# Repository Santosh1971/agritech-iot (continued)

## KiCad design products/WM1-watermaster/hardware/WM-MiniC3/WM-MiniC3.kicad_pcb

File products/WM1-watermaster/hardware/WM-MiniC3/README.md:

# WM-Mini C3 rev A: pump, doser and 4-valve controller (2026-10-27)

A larger FG1. An ESP32-C3 Super Mini (plug-in, USB-C powered) drives six SRD relays through a ULN2003A:
- **K1 PUMP** and **K2 DOSER** switch 230 V.
- **K3–K6** switch 12/24 VAC valves, with one common.

It also has a Hall flow input, a DS1307 RTC with a CR2032, and seven LEDs. The plan and the decisions behind it are in [SPEC.md](SPEC.md) (draft 0.3) and on the "WM-Mini C3 Plan" page.

## Status

| Item | State |
|---|---|
| Schematic | Generated from `tools/design.py`, with wires inside each block and labels only between blocks. **ERC: 0 errors, 0 warnings.** |
| PCB | 99 × 48 mm, 2 layers. Routed with Freerouting, zones filled. **DRC at every severity: 0 violations, 0 unconnected, schematic parity clean** (kicad-cli 9.0.7). |
| 230 V | 5 mm from the pump/doser copper (including their NC pins, which are live while off) to all other copper, enforced by `WM-MiniC3.kicad_dru`. The exceptions are inside K1/K2: 3.5 mm to their own coil pins (the SRD's pinout gives 3.6 mm), and 2.4 mm between pump and doser (the 5.08 mm header has 2.48 mm between its own pads). |
| Panel | `panel/WM-MiniC3-panel.kicad_pcb`, 99 × 98 mm: 2 boards and a 2 mm routed slot with 3 plain tabs (no V-cut, no mouse bites). Board 1 is turned 180°, so both connector edges face outwards. |
| Fab | `fab/`: panel and board Gerbers, schematic PDF, 1:1 prints (top and bottom), BOM, STEP and renders. **Order `WM-MiniC3-panel-gerbers.zip`.** |

## Layout

The board is the draft 0.3 plan **mirrored left to right**. On an upright SRD the NO pin comes out on the left. With the 230 V corner on the left, the pump and doser NO and COM run straight down into their headers without crossing, and still keep 5 mm from the valve header.

- **Bottom left:** K1 PUMP and K2 DOSER, upright, directly above J2 and J3.
- **Top left, above the relays they drive (all > 5 mm from 230 V):**
  - the ULN2003;
  - the six relay LEDs (P D V1 V2 V3 V4) and their resistors;
  - C1, 1000 µF / 16 V (10 mm, 5 mm pitch).
- **Middle, valve block:**
  - K3 V1 and K4 V2 are inverted at the top edge.
  - K5 V3 and K6 V4 are upright below them.
  - All coils meet near the centre line.
- **Top right, next to the ESP:**
  - the CR2032 standing vertical;
  - the DS1307, a through-hole C26 crystal and the I2C pull-ups;
  - the FLOW LED and test pad TP1.
- **Bottom right:** the Super Mini, with USB-C at the bottom edge. Under the module sit the flow-input parts (B5819W, SLCESDB5V0D5 bidirectional 5 V TVS, SOD-523 on hand-solder pads, 10k). IO2 is unused (the AUX pull-up and test pad were removed).
- **+5 V:** 1 mm tracks from the module to all relay coils.
- **Bottom edge, left to right:** J2 PUMP (NO, COM), J3 DOSER (NO, COM), J4 VALVES (COM, V1, V2, V3, V4), J1 FLOW (5V, GND, SIG), USB-C.
- **Holes:** 2 × M3 at (3.5, 24) and (95.5, 24), 92 mm apart, as on the ESP32 test jig.

## Pin map

| GPIO | Net | Function |
|---|---|---|
| IO20 | RLY_PUMP | K1 pump, ULN in 6 / out 11 |
| IO10 | RLY_DOSER | K2 doser, ULN in 5 / out 12 |
| IO1 | RLY_V1 | K5 valve 1, ULN in 4 / out 13, LED D6 |
| IO0 | RLY_V2 | K3 valve 2, ULN in 1 / out 16, LED D7 |
| IO3 | RLY_V3 | K4 valve 3, ULN in 2 / out 15, LED D8 |
| IO4 | RLY_V4 | K6 valve 4, ULN in 3 / out 14, LED D9 |
| IO2 | — | unused (strapping pin, left floating as on Mini-C3) |
| IO5 | FLOW | flow pulses |
| IO6 / IO7 | SDA / SCL | DS1307 |
| IO21 | LED_FLOW | flow LED |
| IO8 | — | on-module LED = WiFi LED |
| IO9 | — | BOOT button = setup button |

## Parts that are not stock KiCad (`ASC.pretty`)

| Part | Footprint |
|---|---|
| Pluggable headers | `Pluggable_2EDGR_5.08_1x0{2,3,5}_Horizontal`: the stackable market header (2EDGR / KF2EDGR), body n × 5.08 mm. It has MSTBA pitch and drills, with round 2.6 mm pads. The pin row is 2.5 mm from the edge; the plug overhangs the board edge. |
| Relays | `Relay_SPDT_SANYOU_SRD_Outline`: KiCad's SRD Form C with the silkscreen cut to the outline, so the K1 PUMP etc. labels fit inside |
| Super Mini | `ESP32-C3_SuperMini_Socket`: from ASC Mini-C3, without its outline silk (that ran past the board edge) |
| CR2032 | `Battery_CR2032_Vertical_3pin`: from ASC Mini-C3 |
| Flow TVS | `D_SOD-523_HandSolder`: SOD-523 with 1.2 × 1.0 mm pads at 2.0 mm pitch for hand soldering (SLKOR SLCESDB5V0D5) |

## Check before ordering

1. **Print `fab/WM-MiniC3-print-1to1.pdf` at 100 %.** Lay on it a real SRD relay, a 2EDGR header, the CR2032 holder and the Super Mini. Pin sides: IO5 and 5V must be at the USB end.
2. **SRD NO pin.** Pad 3 is NO, as on WM1. Check one Rajiv relay (RERL-32) with a meter.
3. **CR2032 holder pins.** The footprint is the Mini-C3 tabbed-cell layout, and its − leg position is provisional. Measure the RBH-2 holder.
4. **C1 size.** The footprint is 10 mm diameter, 5 mm pitch: check your 1000 µF part.
5. **Plug overhang.** The plugs stick out about 8 mm past the bottom edge. Check this against the box wall.
6. **The Super Mini plugs in after the board is screwed down.** Its antenna end sits over the right M3 screw head; a DRC rule ignores that overlap on purpose.

## Regenerate

```bash
cd products/WM1-watermaster/hardware/WM-MiniC3
zsh tools/build.sh 5     # schematic + ERC, then place / route / DRC until clean (Freerouting is not deterministic)
zsh tools/fab.sh         # panel + fab/
```

`tools/clearance_check.py` and `tools/layout_svg.py` are the draft 0.3 planning helpers. They describe the unmirrored plan.

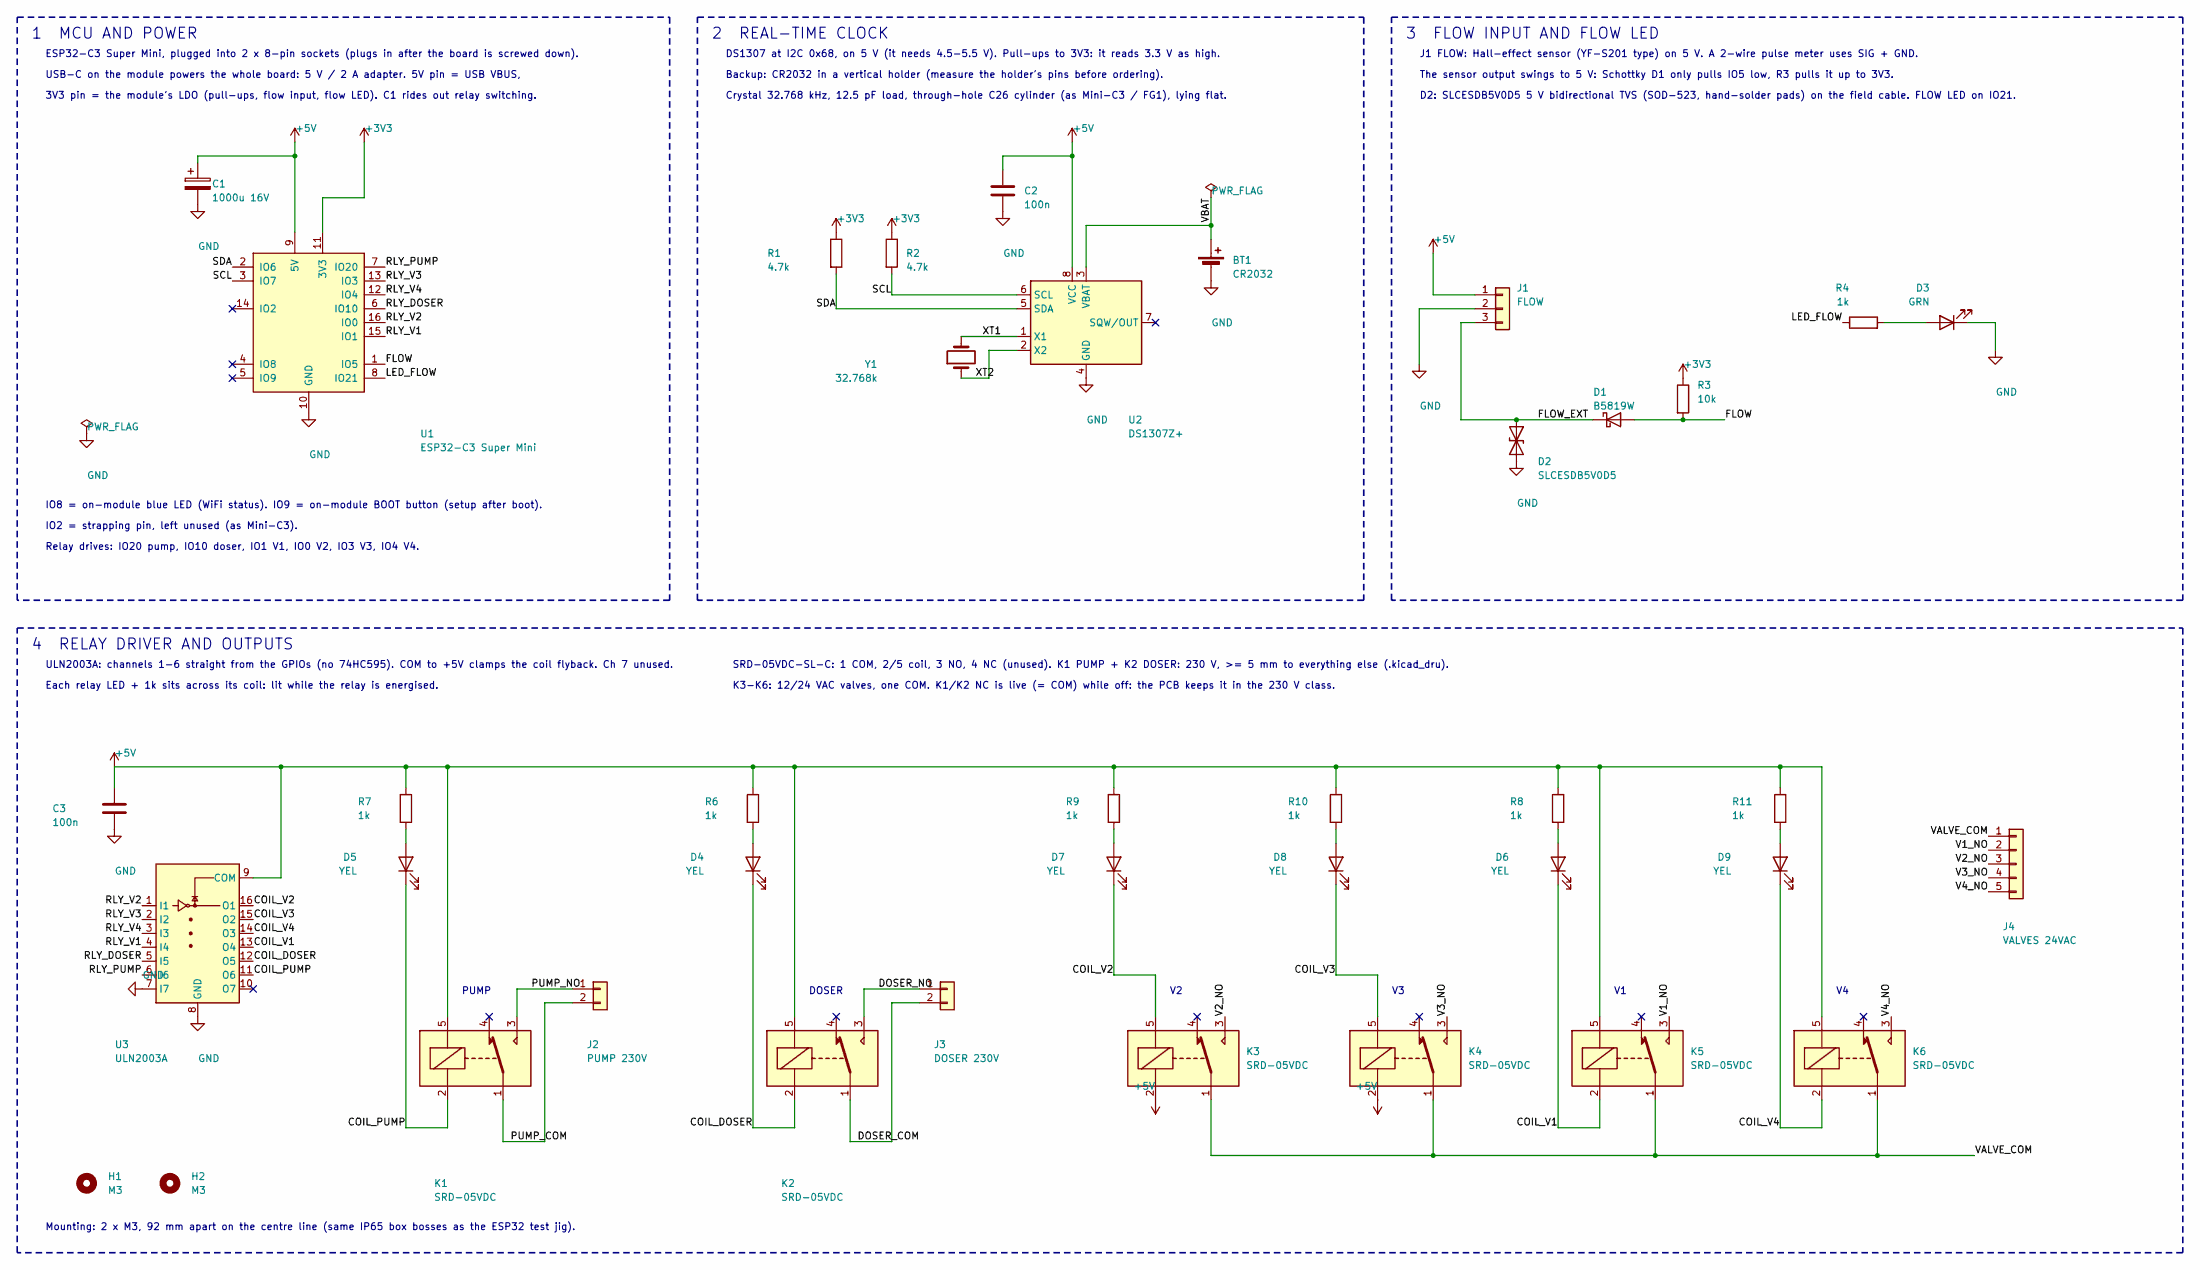
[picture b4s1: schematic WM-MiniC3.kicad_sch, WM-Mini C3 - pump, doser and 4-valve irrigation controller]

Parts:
BT1: CR2032; Battery_CR2032_Vertical_3pin
C1: 1000u 16V; CP_Radial_D10.0mm_P5.00mm
C2, C3: 100n; C_0805_2012Metric
D1: B5819W; D_SOD-123
D2: SLCESDB5V0D5; D_SOD-523_HandSolder
D3: GRN; LED_1206_3216Metric
D4, D5, D6, D7, D8, D9: YEL; LED_1206_3216Metric
H1, H2: M3; MountingHole_3.2mm_M3
J1: FLOW; Pluggable_2EDGR_5.08_1x03_Horizontal
J2: PUMP 230V; Pluggable_2EDGR_5.08_1x02_Horizontal
J3: DOSER 230V; Pluggable_2EDGR_5.08_1x02_Horizontal
J4: VALVES 24VAC; Pluggable_2EDGR_5.08_1x05_Horizontal
K1, K2, K3, K4, K5, K6: SRD-05VDC; Relay_SPDT_SANYOU_SRD_Outline
R1, R2: 4.7k; R_0805_2012Metric
R3: 10k; R_0805_2012Metric
R4, R6, R7, R8, R9, R10, R11: 1k; R_0805_2012Metric
U1: ESP32-C3 Super Mini; ESP32-C3_SuperMini_Socket
U2: DS1307Z+; SOIC-8_3.9x4.9mm_P1.27mm
U3: ULN2003A; SOIC-16_3.9x9.9mm_P1.27mm
Y1: 32.768k; Crystal_C26-LF_D2.1mm_L6.5mm_Horizontal

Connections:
+3V3: R1.1, R2.1, R3.1, U1.11 (3V3)
+5V: C1.1, C2.1, C3.1, J1.1, K1.5, K2.5, K3.2, K4.2, K5.5, K6.5, R6.1, R7.1, R8.1, R9.1, R10.1, R11.1, U1.9 (5V), U2.8 (VCC), U3.9 (COM)
/COIL_DOSER: D4.1 (K), K2.2, U3.12 (O5)
/COIL_PUMP: D5.1 (K), K1.2, U3.11 (O6)
/COIL_V1: D6.1 (K), K5.2, U3.13 (O4)
/COIL_V2: D7.1 (K), K3.5, U3.16 (O1)
/COIL_V3: D8.1 (K), K4.5, U3.15 (O2)
/COIL_V4: D9.1 (K), K6.2, U3.14 (O3)
/DOSER_COM: J3.2, K2.1
/DOSER_NO: J3.1, K2.3
/FLOW: D1.2 (A), R3.2, U1.1 (IO5)
/FLOW_EXT: D1.1 (K), D2.1 (A1), J1.3
/LED_FLOW: R4.1, U1.8 (IO21)
/PUMP_COM: J2.2, K1.1
/PUMP_NO: J2.1, K1.3
/RLY_DOSER: U1.6 (IO10), U3.5 (I5)
/RLY_PUMP: U1.7 (IO20), U3.6 (I6)
/RLY_V1: U1.15 (IO1), U3.4 (I4)
/RLY_V2: U1.16 (IO0), U3.1 (I1)
/RLY_V3: U1.13 (IO3), U3.2 (I2)
/RLY_V4: U1.12 (IO4), U3.3 (I3)
/SCL: R2.2, U1.3 (IO7), U2.6 (SCL)
/SDA: R1.2, U1.2 (IO6), U2.5 (SDA)
/V1_NO: J4.2, K5.3
/V2_NO: J4.3, K3.3
/V3_NO: J4.4, K4.3
/V4_NO: J4.5, K6.3
/VALVE_COM: J4.1, K3.1, K4.1, K5.1, K6.1
/VBAT: BT1.1 (+), U2.3 (VBAT)
/XT1: U2.1 (X1), Y1.2
/XT2: U2.2 (X2), Y1.1
GND: BT1.2 (-), C1.2, C2.2, C3.2, D2.2 (A2), D3.1 (K), J1.2, U1.10 (GND), U2.4 (GND), U3.7 (I7), U3.8 (GND)
unnamed: D3.2 (A), R4.2
unnamed: D4.2 (A), R6.2
unnamed: D5.2 (A), R7.2
unnamed: D6.2 (A), R8.2
unnamed: D7.2 (A), R9.2
unnamed: D8.2 (A), R10.2
unnamed: D9.2 (A), R11.2

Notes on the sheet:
ESP32-C3 Super Mini, plugged into 2 x 8-pin sockets (plugs in after the board is screwed down).
USB-C on the module powers the whole board: 5 V / 2 A adapter. 5V pin = USB VBUS,
3V3 pin = the module's LDO (pull-ups, flow input, flow LED). C1 rides out relay switching.
IO8 = on-module blue LED (WiFi status). IO9 = on-module BOOT button (setup after boot).
IO2 = strapping pin, left unused (as Mini-C3).
Relay drives: IO20 pump, IO10 doser, IO1 V1, IO0 V2, IO3 V3, IO4 V4.
DS1307 at I2C 0x68, on 5 V (it needs 4.5-5.5 V). Pull-ups to 3V3: it reads 3.3 V as high.
Backup: CR2032 in a vertical holder (measure the holder's pins before ordering).
Crystal 32.768 kHz, 12.5 pF load, through-hole C26 cylinder (as Mini-C3 / FG1), lying flat.
J1 FLOW: Hall-effect sensor (YF-S201 type) on 5 V. A 2-wire pulse meter uses SIG + GND.
The sensor output swings to 5 V: Schottky D1 only pulls IO5 low, R3 pulls it up to 3V3.
D2: SLCESDB5V0D5 5 V bidirectional TVS (SOD-523, hand-solder pads) on the field cable. FLOW LED on IO21.
ULN2003A: channels 1-6 straight from the GPIOs (no 74HC595). COM to +5V clamps the coil flyback. Ch 7 unused.
Each relay LED + 1k sits across its coil: lit while the relay is energised.
SRD-05VDC-SL-C: 1 COM, 2/5 coil, 3 NO, 4 NC (unused). K1 PUMP + K2 DOSER: 230 V, >= 5 mm to everything else (.kicad_dru).
K3-K6: 12/24 VAC valves, one COM. K1/K2 NC is live (= COM) while off: the PCB keeps it in the 230 V class.
PUMP
DOSER
Mounting: 2 x M3, 92 mm apart on the centre line (same IP65 box bosses as the ESP32 test jig).
1 MCU AND POWER
2 REAL-TIME CLOCK
3 FLOW INPUT AND FLOW LED
4 RELAY DRIVER AND OUTPUTS

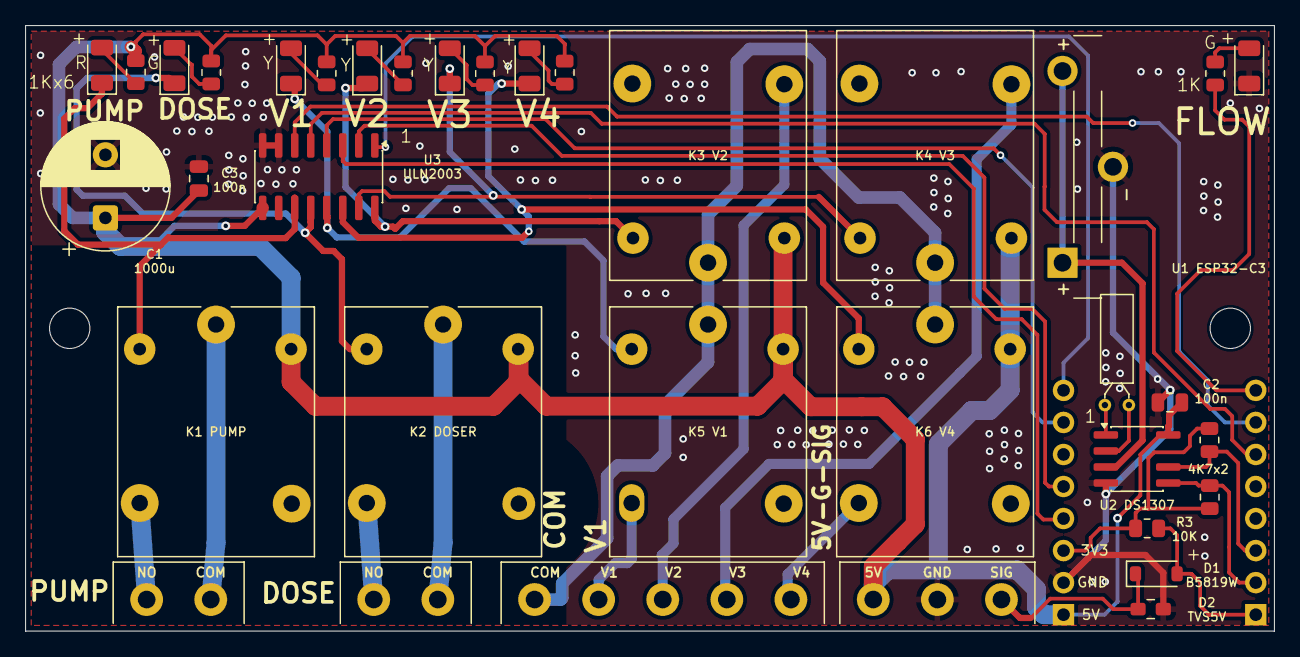
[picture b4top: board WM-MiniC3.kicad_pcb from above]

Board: 2 copper layers, 99.0 x 48.0 mm, 39 parts (0 on the bottom side), 39 nets.

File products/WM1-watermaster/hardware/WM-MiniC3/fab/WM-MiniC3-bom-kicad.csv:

"Reference","Value","Footprint","QUANTITY"
"BT1","CR2032","ASC:Battery_CR2032_Vertical_3pin","1"
"C1","1000u 16V","Capacitor_THT:CP_Radial_D10.0mm_P5.00mm","1"
"C2,C3","100n","Capacitor_SMD:C_0805_2012Metric","2"
"D1","B5819W","Diode_SMD:D_SOD-123","1"
"D2","SLCESDB5V0D5","ASC:D_SOD-523_HandSolder","1"
"D3","GRN","LED_SMD:LED_1206_3216Metric","1"
"D4-D9","YEL","LED_SMD:LED_1206_3216Metric","6"
"J1","FLOW","ASC:Pluggable_2EDGR_5.08_1x03_Horizontal","1"
"J2","PUMP 230V","ASC:Pluggable_2EDGR_5.08_1x02_Horizontal","1"
"J3","DOSER 230V","ASC:Pluggable_2EDGR_5.08_1x02_Horizontal","1"
"J4","VALVES 24VAC","ASC:Pluggable_2EDGR_5.08_1x05_Horizontal","1"
"K1-K6","SRD-05VDC","ASC:Relay_SPDT_SANYOU_SRD_Outline","6"
"R1,R2","4.7k","Resistor_SMD:R_0805_2012Metric","2"
"R3","10k","Resistor_SMD:R_0805_2012Metric","1"
"R4,R6-R11","1k","Resistor_SMD:R_0805_2012Metric","7"
"U1","ESP32-C3 Super Mini","ASC:ESP32-C3_SuperMini_Socket","1"
"U2","DS1307Z+","Package_SO:SOIC-8_3.9x4.9mm_P1.27mm","1"
"U3","ULN2003A","Package_SO:SOIC-16_3.9x9.9mm_P1.27mm","1"
"Y1","32.768k","Crystal:Crystal_C26-LF_D2.1mm_L6.5mm_Horizontal","1"

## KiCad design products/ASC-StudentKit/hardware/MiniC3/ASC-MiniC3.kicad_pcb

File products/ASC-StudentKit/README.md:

# ASC-StudentKit

These are the student kits (**Mini** and **Mega**) for the Student Product Studio (`docs/student-product-studio.md`). Each kit is a carrier board built on an ESP32-S3, plus starter modules and a ready-made enclosure. Agri Sensors and Controls supplies the kits to colleges, priced per batch.

The kits are also **Project #0** of the studio: they are designed by following the same stages a student follows.

- `docs/StudentKit_Specification_v0.1.md`: system specification with hardware, software and mechanical requirements. It is a draft, and the open decisions are listed in §8.
- `docs/StudentKit_Architecture_v0.1.md`: architecture (stage 3), covering block diagrams, pin map, connectors, power budget and battery life.
- `hardware/pinmap.json`: the pin map for both boards, checked by `python3 hardware/tools/check_pinmap.py`.
- `firmware/`: the ASC Studio firmware, one image for both kits and the DevKit stand-in. See `firmware/README.md` for the build and the serial protocol.
- `mobile-app/asc_studio_app/`: the shared ASC Studio phone app (Flutter, Android, spec §5A). It builds each student's screen from the layout in their design.

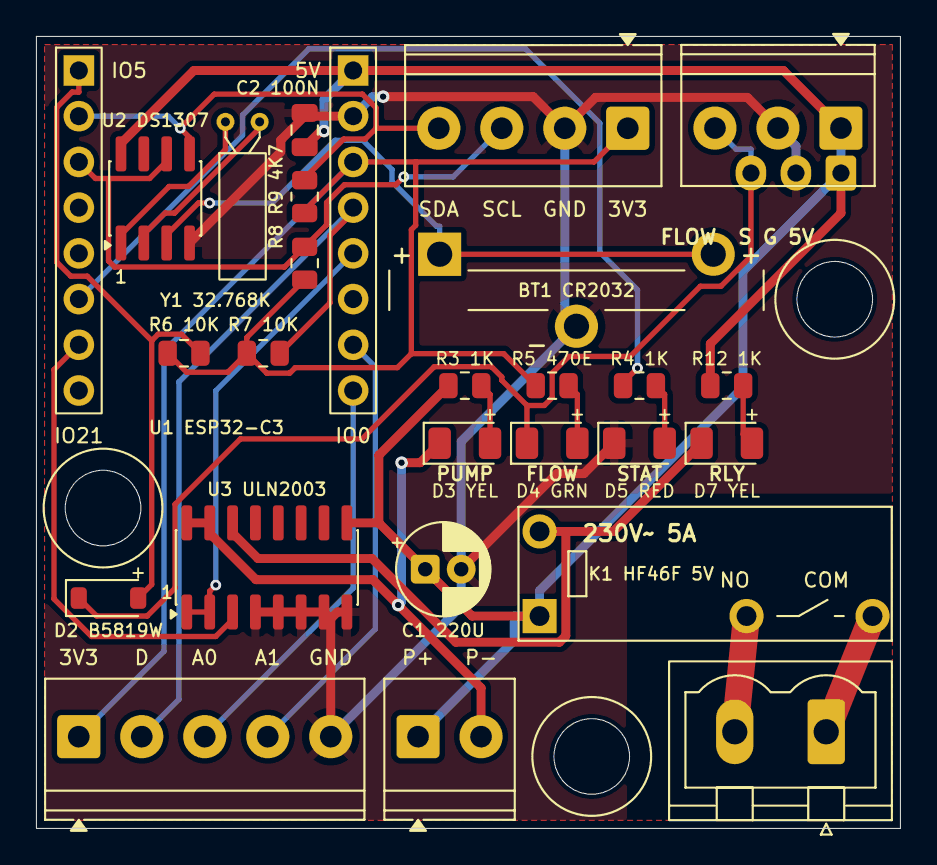
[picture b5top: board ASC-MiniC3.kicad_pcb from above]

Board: 2 copper layers, 48.0 x 44.0 mm, 29 parts (0 on the bottom side), 24 nets.

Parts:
BT1: CR2032 tabbed; Battery_CR2032_Vertical_3pin
C1: 220u 10V; CP_Radial_D5.0mm_P2.00mm
C2: 100n; C_0805_2012Metric
D2: B5819W; D_SOD-123
D3: PUMP yellow; LED_1206_3216Metric
D4: FLOW yellow-green; LED_1206_3216Metric
D5: STATUS red; LED_1206_3216Metric
D7: RELAY yellow; LED_1206_3216Metric
H1, H2, H3: SNAP 4.2; Snap_Standoff_4.2mm
J1: PUMP; TerminalBlock_Phoenix_PT-1,5-2-3.5-H_1x02_P3.50mm_Horizontal
J3: AUX; TerminalBlock_Phoenix_PT-1,5-5-3.5-H_1x05_P3.50mm_Horizontal
J4: FLOW (XH or 3.5 mm); Flow_XH3_or_PT-1,5-3-3.5mm
J5: I2C; TerminalBlock_Phoenix_PT-1,5-4-3.5-H_1x04_P3.50mm_Horizontal
J6: RELAY 230V (MSTBVA); PhoenixContact_MSTBVA_2,5_2-G-5,08_1x02_P5.08mm_Vertical
K1: HF46F/005-HS1; Relay_SPST_Hongfa_HF46F
R3, R4, R12: 1k; R_0805_2012Metric
R5: 470; R_0805_2012Metric
R6, R7: 10k; R_0805_2012Metric
R8, R9: 4.7k; R_0805_2012Metric
U1: ESP32-C3 Super Mini; ESP32-C3_SuperMini_Socket
U2: DS1307Z+; SOIC-8_3.9x4.9mm_P1.27mm
U3: ULN2003A; SOIC-16_3.9x9.9mm_P1.27mm
Y1: 32.768k 12.5pF; Crystal_C26-LF_D2.1mm_L6.5mm_Horizontal

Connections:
+3V3: J3.1, J5.1, R5.1, R6.1, R7.1, R8.1, R9.1, U1.11
+5V: C1.1, C2.1, J1.1, J4.1, K1.1, R3.1, R12.1, U1.9, U2.8, U3.9
/AUX_A0: J3.3, U1.16
/AUX_A1: J3.4, U1.15
/AUX_D: J3.2, R7.2, U1.12
/FLOW: D2.2, R6.2, U1.1
/FLOW_EXT: D2.1, D4.1, J4.3
/LED_FLOW_A: D4.2, R5.2
/LED_PUMP_A: D3.2, R3.2
/LED_RLY_A: D7.2, R12.2
/LED_STATUS: R4.1, U1.6
/LED_STATUS_A: D5.2, R4.2
/PUMP: U1.13, U3.1, U3.2
/PUMP_N: D3.1, J1.2, U3.15, U3.16
/RELAY: U1.7, U3.3
/RELAY_COIL: D7.1, K1.2, U3.14
/RELAY_COM: J6.1, K1.4
/RELAY_NO: J6.2, K1.3
/SCL: J5.3, R9.2, U1.3, U2.6
/SDA: J5.4, R8.2, U1.2, U2.5
/VBAT: BT1.1, U2.3
/XT1: U2.1, Y1.1
/XT2: U2.2, Y1.2
GND: BT1.2, C1.2, C2.2, D5.1, J3.5, J4.2, J5.2, U1.10, U2.4, U3.4, U3.5, U3.6, U3.7, U3.8

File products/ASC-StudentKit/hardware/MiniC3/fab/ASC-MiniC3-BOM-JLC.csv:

Comment,Designator,Footprint,LCSC Part #
100n,C2,C_0805_2012Metric,C49678
10k,"R6,R7",R_0805_2012Metric,C17414
1k,"R3,R4,R12",R_0805_2012Metric,C17513
4.7k,"R8,R9",R_0805_2012Metric,C17673
470,R5,R_0805_2012Metric,C17710
B5819W,D2,D_SOD-123,C8598
DS1307Z+,U2,SOIC-8_3.9x4.9mm_P1.27mm,C49375271 (MSKSEMI DS1307Z+MSK)
FLOW yellow-green,D4,LED_1206_3216Metric,C28310441
PUMP yellow,D3,LED_1206_3216Metric,C30584802
RELAY yellow,D7,LED_1206_3216Metric,C30584802
STATUS red,D5,LED_1206_3216Metric,C37635751
ULN2003A,U3,SOIC-16_3.9x9.9mm_P1.27mm,C7512

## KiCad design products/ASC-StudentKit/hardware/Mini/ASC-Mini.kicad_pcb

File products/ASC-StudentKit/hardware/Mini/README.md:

# ASC Mini rev A: schematic

The Mini carrier board for the ASC Student Kit. It is a half board, **97.4 × 47.0 mm**, held by **3 × M3** on the box's upper three bosses. Two Minis fit on one 100 × 100 mm panel (kit architecture §8).

## Status

| Item | State |
|---|---|
| Schematic | **First draft, generated.** 92 parts, 55 nets. `tools/check_design.py` and `tools/check_sheet.py` pass. **KiCad's ERC has not been run yet** (no KiCad 9 in the build container). Run it on the Mac first. |
| Pin map | Matches `../pinmap.json` (board `mini`), checked by `tools/check_design.py` |
| Footprints | 0402 resistors and small capacitors. J3 (the tester's pins) is a row of SMD pads on the back under the module, not fitted (DNP). The RTC cell holder is the flat Keystone 3034 on the back. 25 come from the KiCad 9.0.9 library. The HF46F relay footprint is our own (`ASC.pretty`), drawn from the Hongfa datasheet's PCB layout; check it against a real relay before ordering. The Grove socket uses a JST-PH 4-pin footprint as a stand-in; swap it for the HY2.0-4P part at layout. |
| PCB | **Routed, 2 layers, 1.6 mm.** 97.4 × 47.0 mm, 3 × M3. 1581 tracks (narrowest 0.15 mm), 287 vias (0.55 / 0.3 mm), clearance 0.15 mm. GND is joined by tracks as well as the pours on both layers. All checks below pass. **KiCad's zone fill and DRC have not been run yet** (no KiCad in the build container); run them on the Mac before ordering. |

## What is on it

| Block | Parts | Notes |
|---|---|---|
| 12 V input | J1 2-way 5.08 mm terminal, D1 SS34 (reverse polarity), D2 SMAJ26A (TVS), C1–C3 | **9–24 V in, 24 V maximum.** A terminal rather than a barrel jack, so the cable comes through a gland. |
| 12 V → 5 V | U2 TPS54202 buck (28 V max, 2 A), L1 10 µH, R1/R2 set **5.3 V**, D3 SS34 | The diode drop leaves about 5.0 V on +5V |
| USB-C | J2, R3/R4 5.1 k CC pull-downs, F1 0.5 A PTC, D4 SS34, U3 USBLC6-2SC6 ESD | Flashing and the console over native USB (GPIO19/20); also powers the board on a desk. D3 and D4 OR the two 5 V sources. |
| 5 V → 3.3 V | U4 AP7361C-33E (1 A LDO) | ESP32-S3 WiFi peaks of ≈350 mA, plus the RTC and the 3.3 V sensors |
| MCU | U1 ESP32-S3-MINI-1-**N8** | EN: R8/C14 plus a **RESET** button. GPIO0: R9 plus the **PAIR/BOOT** button. |
| Board ID | R10 30 k / R11 10 k = 0.25 × 3V3 on GPIO11 | The firmware reads this as "mini" |
| 12 V sense | R5 100 k / R6 10 k on GPIO10 | 24 V reads 2.18 V; 0 V means USB power only |
| RTC | U5 DS3231MZ+ (SOIC-8), BT1 CR2032 **on the back**, INT/SQW → GPIO16 | Internal I²C bus (GPIO12/13, 4.7 k pull-ups) |
| Sensor ports S1–S4 | J4–J7 JST-XH 4-pin: 1 GND · 2 3V3 · 3 5V · 4 SIG | SIG: 470 Ω in series, BAT54S clamps to 3V3 and GND, so a 5 V digital signal such as a flow sensor is safe. Port supplies fused: F2 0.5 A (5 V), F3 0.2 A (3V3). |
| I2C-1 student port | J8 Grove pinout: 1 SCL · 2 SDA · 3 3V3 · 4 GND | Its own bus (GPIO14/15), 4.7 k pull-ups |
| Relays OUT1/OUT2 | K1/K2 **Hongfa HF46F/005-HS1** (1 Form A, 5 A, 20.5 × 7.2 mm, 40 mA coil), Q2/Q3 AO3400A, D12/D13 flyback, J9/J10 2-way terminals (COM · NO) | GPIO35/36, gate pull-downs so the relays stay off through reset. Normally open only, which is all the rules use. **LOW VOLTAGE ONLY** on the silkscreen. |
| Buzzer | BZ1 5 V active 12 mm, Q1 AO3400A, D7 | GPIO46 is a strapping pin: R14 holds it low at reset |
| LEDs, seen through the clear lid | D5 **PWR**, D6 **STATUS** (GPIO48), D14 **OUT1**, D15 **OUT2** (on the relay coils, so they need no GPIO) | Each LED's name goes on the silkscreen (the `Silk` field on each part) |
| Test header | J3 1.27 mm × 8: 3V3, GND, EN, PAIR, D−, D+, TX, RX | The production tester's pogo pins, the same set as AWD1 |
| Mounting | H1–H3 M3 | Positions in `design.py` |

## Decided

- **Relays:** Hongfa HF46F (2026-10-08). It replaces the SRD and saves about 300 mm² of board.
- **Input:** 24 V maximum (2026-10-08). The TPS54202 (28 V) and the SMAJ26A suit that.
- **No OLED** in the kits (2026-10-08). The phone app is the screen, and the LEDs show through the clear lid.

## Please review

1. **Connector row.** The bottom edge has room for about 78 mm of connectors between the screw bosses. The three terminals (OUT1, OUT2, 12 V IN) need about 31 mm. The four XH ports and the Grove socket need about 58 mm more. Proposal: terminals along the bottom edge, and the XH and Grove sockets (vertical) in a second row just above them, with cables running down past the edge. USB-C goes on a side edge.
2. **HF46F footprint.** Print the footprint at 1:1 and push a real relay's pins through the paper before the first order.

## On the Mac, before ordering

1. Open `ASC-Mini.kicad_pro` in KiCad 9.
2. In the PCB editor press **B** to fill the zones (GND on both layers).
3. Run **Inspect → Design Rules Checker**. Expect nothing but silkscreen cosmetics. The USB-C footprint's own pads sit exactly 0.2 mm apart, which is fine under the 0.15 mm rule.
4. Check the HF46F relay footprint against a real relay (print 1:1).
5. Plot gerbers and drill files, or use the JLC plugin. Order 2 boards per 100 × 100 mm panel (architecture §8).

## Regenerate

```bash
cd products/ASC-StudentKit/hardware/Mini
python3 tools/gen_sch.py          # ASC-Mini.kicad_sch and tools/netlist.json
python3 tools/check_design.py     # pins vs pinmap.json, nets, power, strapping pins
python3 tools/check_sheet.py      # no accidental connections or overlaps on the sheet
python3 tools/gen_pcb.py          # ASC-Mini.kicad_pcb: outline, holes, placement, zones, labels (unrouted)
```

The board is routed by these steps. Freerouting 2.5.0 comes from Maven Central and needs Java 25:

```bash
export FREEROUTING_JAR=…/freerouting-2.5.0-executable.jar JAVA=…/java-25/bin/java
ROUTE_STAGE=signals POWER_W=0.45 SUPPLY_W=0.3 CLEARANCE=0.19 VIA_D=0.55 python3 tools/route.py   # every net but GND
python3 tools/patch_route.py                              # A* grid router with rip-up: whatever Freerouting left open
ROUTE_STAGE=gnd python3 tools/route.py                    # GND as tracks around the signals
PATCH_FINE=1 PATCH_CLR=0.16 python3 tools/patch_route.py GND
python3 tools/nudge_vias.py                               # move any via the grid left too close
```

Freerouting's result changes a lot with small inputs. The `ROUTE_TAG` and `ROUTE_ONLY` options run several variants side by side, so the best one can be imported. After a part moves, `tools/carry_routing.py OLD.kicad_pcb` keeps the existing routing except near the moved part, and `patch_route.py` reconnects the rest.

Checks, all passing on the committed board:

```bash
python3 tools/check_connect.py --include-gnd   # every net joined by copper (the module's GND pads are tied inside it)
python3 tools/check_clearance.py               # tracks, vias and pads of different nets ≥ 0.15 mm; edge; holes
python3 tools/check_board.py                   # pads clear of the edge and the screw heads
python3 tools/check_pour.py                    # GND is one piece; no dead pour patches or vias
```

`gen_sch.py` reads KiCad's symbol libraries from `KICAD_SYMBOL_DIR`. The default is KiCad 9 on macOS (`/Applications/KiCad/KiCad.app/Contents/SharedSupport/symbols`).

Then open `ASC-Mini.kicad_pro` in KiCad 9 and run **Inspect → Electrical Rules Checker**.

Edit `tools/design.py` and regenerate, rather than editing the schematic by hand, until the board layout starts. After that, switch to editing in KiCad, as AWD1 did.

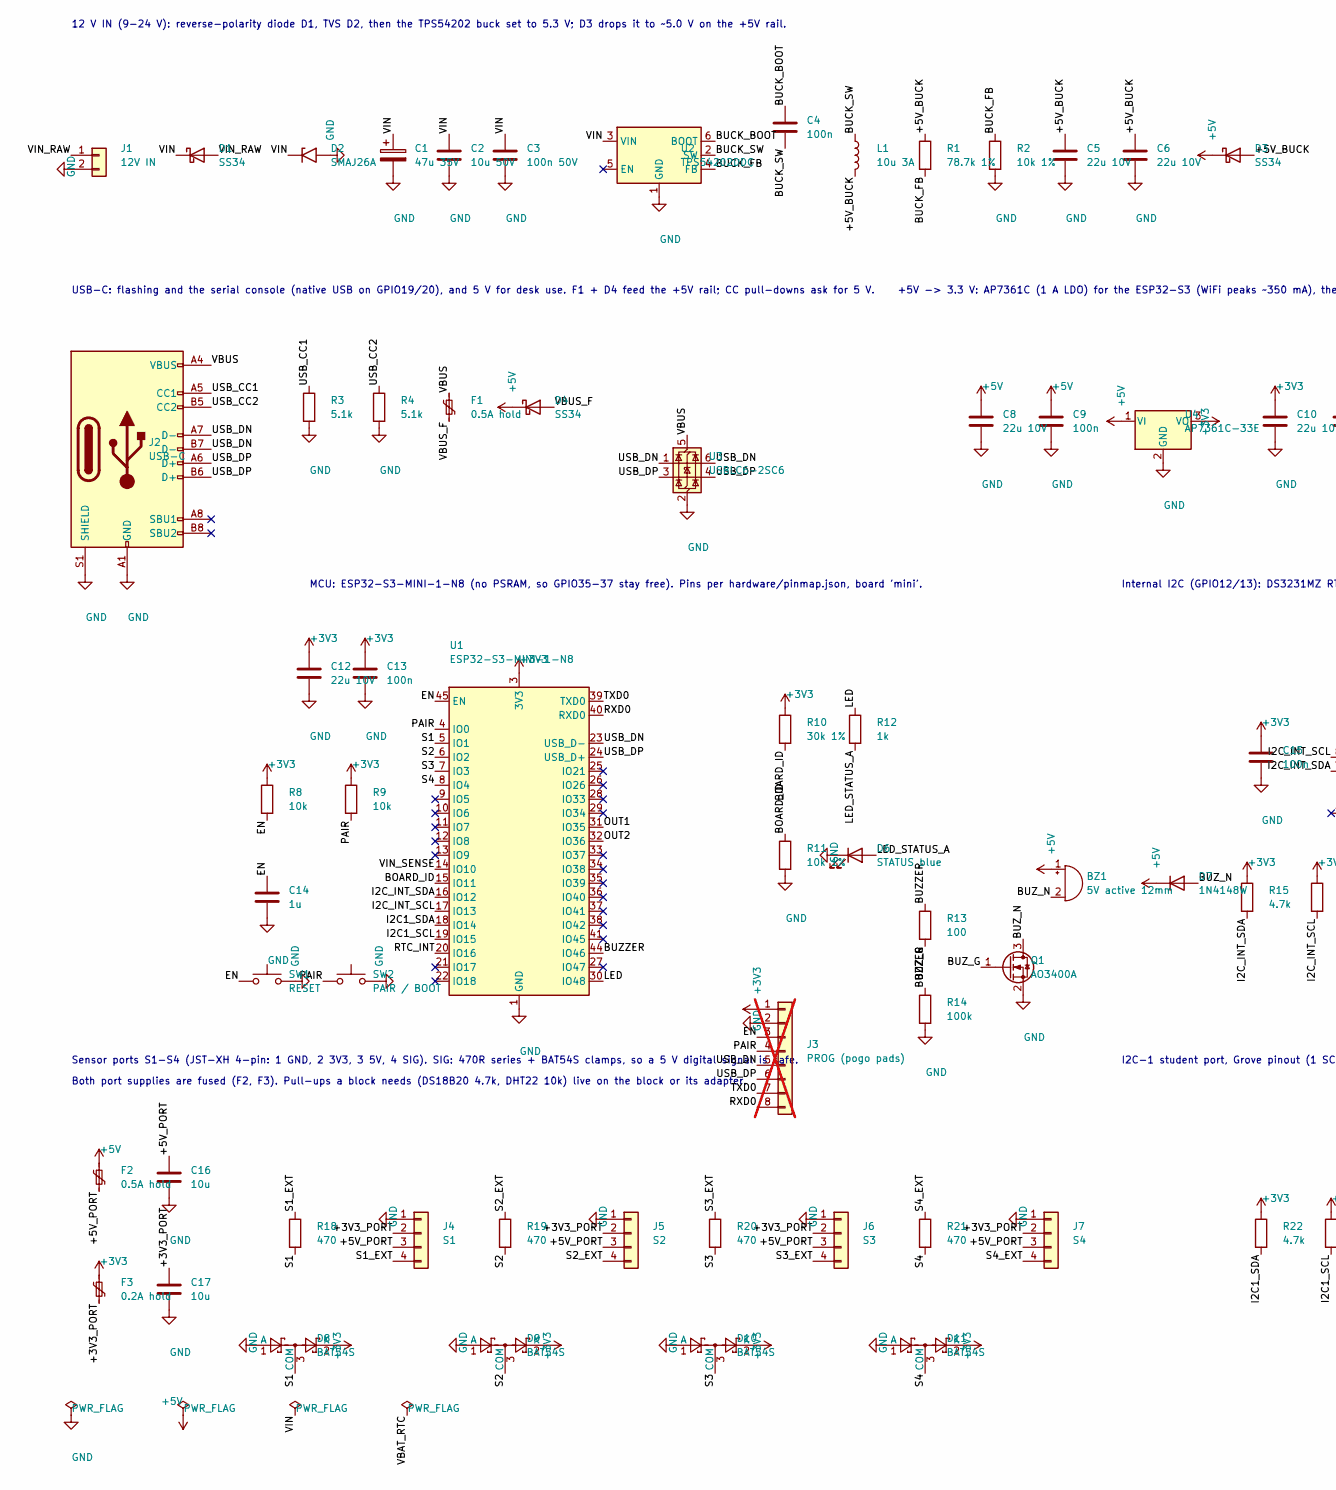
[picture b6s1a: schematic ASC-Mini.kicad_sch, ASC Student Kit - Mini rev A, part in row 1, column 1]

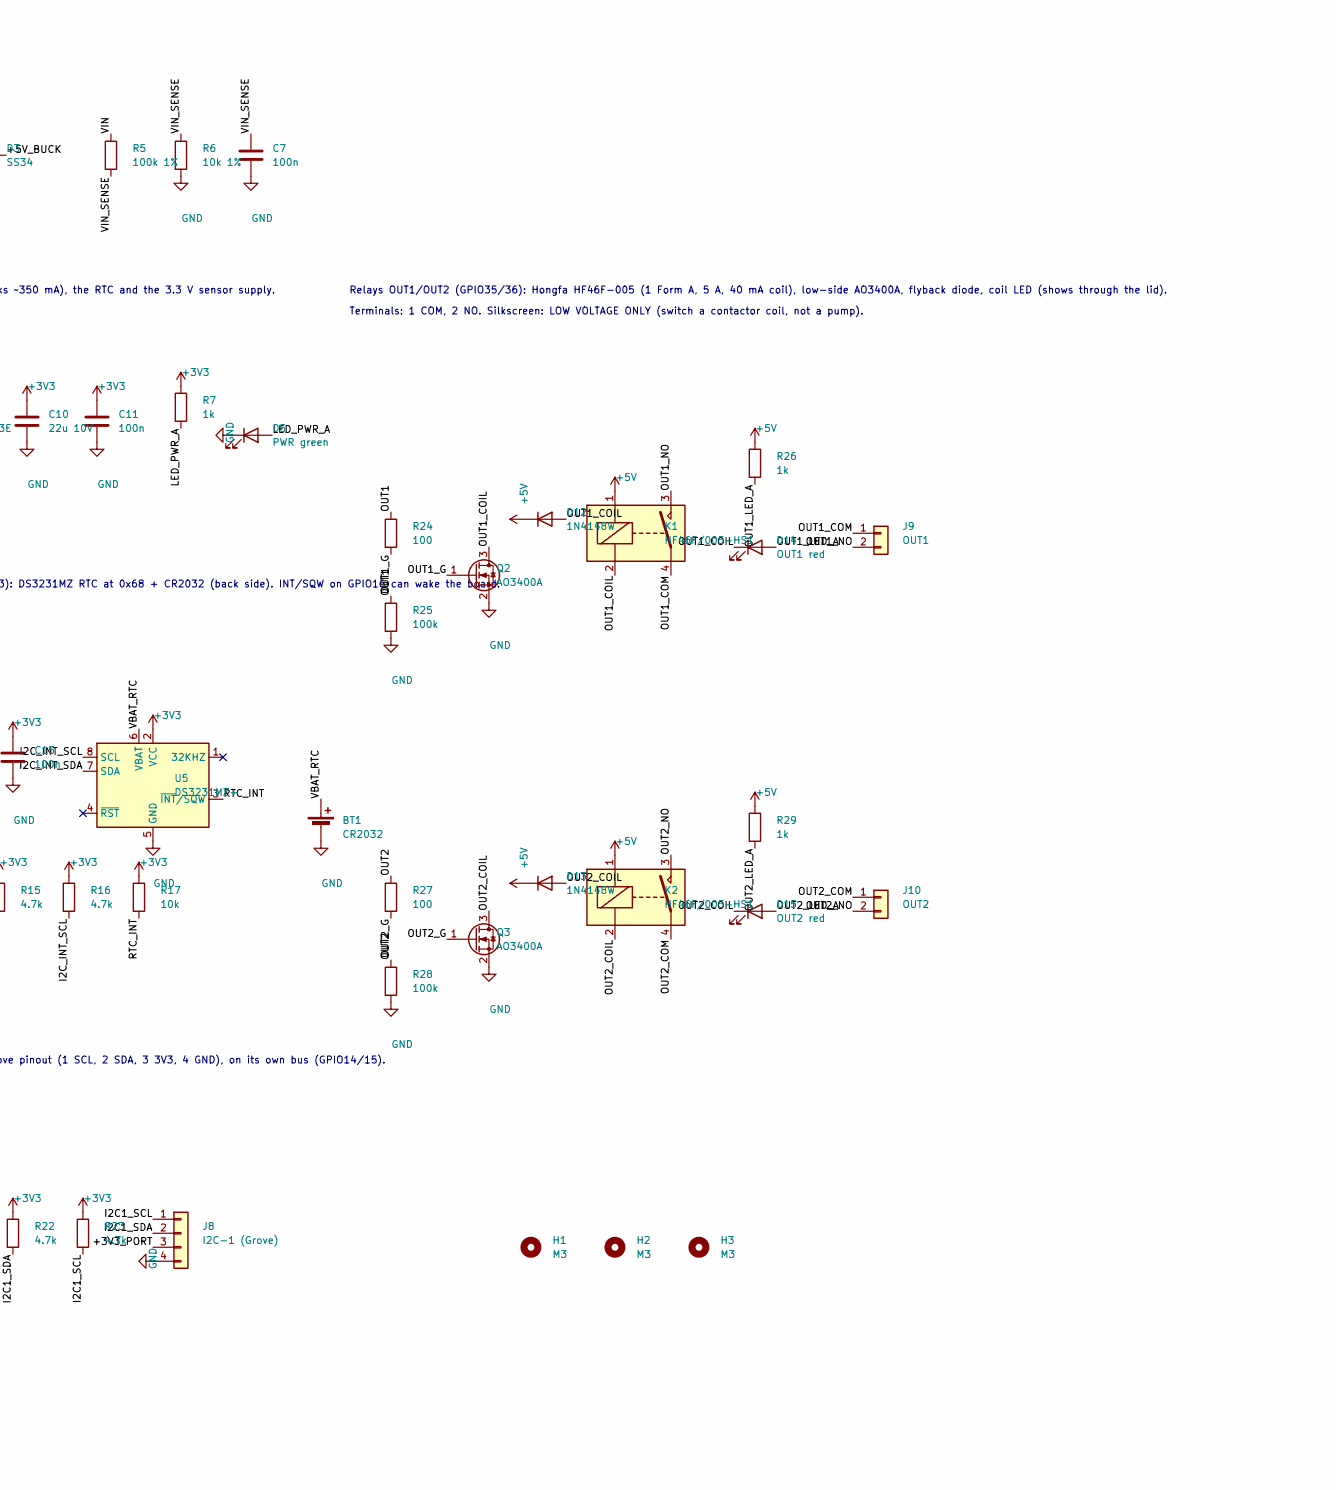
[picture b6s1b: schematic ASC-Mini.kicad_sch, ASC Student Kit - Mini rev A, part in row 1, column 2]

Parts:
BT1: CR2032; BatteryHolder_Keystone_3034_1x20mm
BZ1: 5V active 12mm; Buzzer_12x9.5RM7.6
C1: 47u 35V; CP_Elec_6.3x5.4
C2: 10u 50V; C_1206_3216Metric
C3: 100n 50V; C_0402_1005Metric
C4, C7, C9, C11, C13, C15: 100n; C_0402_1005Metric
C5, C6, C8, C10, C12: 22u 10V; C_1206_3216Metric
C14: 1u; C_0402_1005Metric
C16, C17: 10u; C_0805_2012Metric
D1, D3, D4: SS34; D_SMA
D2: SMAJ26A; D_SMA
D5: PWR green; LED_0805_2012Metric
D6: STATUS blue; LED_0805_2012Metric
D7, D12, D13: 1N4148W; D_SOD-123
D8, D9, D10, D11: BAT54S; SOT-23
D14: OUT1 red; LED_0805_2012Metric
D15: OUT2 red; LED_0805_2012Metric
F1, F2: 0.5A hold; Fuse_1206_3216Metric
F3: 0.2A hold; Fuse_1206_3216Metric
H1, H2, H3: M3; MountingHole_3.2mm_M3
J1: 12V IN; PhoenixContact_MSTBA_2,5_2-G-5,08_1x02_P5.08mm_Horizontal
J2: USB-C; USB_C_Receptacle_HRO_TYPE-C-31-M-12
J3: PROG (pogo pads); PinHeader_1x08_P1.27mm_Vertical_SMD_Pin1Left; not fitted
J4: S1; JST_XH_B4B-XH-A_1x04_P2.50mm_Vertical
J5: S2; JST_XH_B4B-XH-A_1x04_P2.50mm_Vertical
J6: S3; JST_XH_B4B-XH-A_1x04_P2.50mm_Vertical
J7: S4; JST_XH_B4B-XH-A_1x04_P2.50mm_Vertical
J8: I2C-1 (Grove); JST_PH_B4B-PH-K_1x04_P2.00mm_Vertical
J9: OUT1; PhoenixContact_MSTBA_2,5_2-G-5,08_1x02_P5.08mm_Horizontal
J10: OUT2; PhoenixContact_MSTBA_2,5_2-G-5,08_1x02_P5.08mm_Horizontal
K1, K2: HF46F/005-HS1; Relay_SPST_Hongfa_HF46F
L1: 10u 3A; L_6.3x6.3_H3
Q1, Q2, Q3: AO3400A; SOT-23
R1: 78.7k 1%; R_0402_1005Metric
R2, R6, R11: 10k 1%; R_0402_1005Metric
R3, R4: 5.1k; R_0402_1005Metric
R5: 100k 1%; R_0402_1005Metric
R7, R12, R26, R29: 1k; R_0402_1005Metric
R8, R9, R17: 10k; R_0402_1005Metric
R10: 30k 1%; R_0402_1005Metric
R13, R24, R27: 100; R_0402_1005Metric
R14, R25, R28: 100k; R_0402_1005Metric
R15, R16, R22, R23: 4.7k; R_0402_1005Metric
R18, R19, R20, R21: 470; R_0402_1005Metric
SW1: RESET; SW_SPST_TL3342
SW2: PAIR / BOOT; SW_SPST_TL3342
U1: ESP32-S3-MINI-1-N8; ESP32-S2-MINI-1
U2: TPS54202DDC; SOT-23-6
U3: USBLC6-2SC6; SOT-23-6
U4: AP7361C-33E; SOT-223-3_TabPin2
U5: DS3231MZ+; SOIC-8_3.9x4.9mm_P1.27mm

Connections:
+3V3: C10.1, C11.1, C12.1, C13.1, C15.1, D8.2 (K), D9.2 (K), D10.2 (K), D11.2 (K), F3.1, J3.1, R7.1, R8.1, R9.1, R10.1, R15.1, R16.1, R17.1, R22.1, R23.1, U1.3 (3V3), U4.3 (VO), U5.2 (VCC)
+5V: BZ1.1 (+), C8.1, C9.1, D3.1 (K), D4.1 (K), D7.1 (K), D12.1 (K), D13.1 (K), F2.1, K1.1, K2.1, R26.1, R29.1, U4.1 (VI)
/+3V3_PORT: C17.1, F3.2, J4.2, J5.2, J6.2, J7.2, J8.3
/+5V_BUCK: C5.1, C6.1, D3.2 (A), L1.2, R1.1
/+5V_PORT: C16.1, F2.2, J4.3, J5.3, J6.3, J7.3
/BOARD_ID: R10.2, R11.1, U1.15 (IO11)
/BUCK_BOOT: C4.1, U2.6 (BOOT)
/BUCK_FB: R1.2, R2.1, U2.4 (FB)
/BUCK_SW: C4.2, L1.1, U2.2 (SW)
/BUZZER: R13.1, R14.1, U1.44 (IO46)
/BUZ_G: Q1.1 (G), R13.2
/BUZ_N: BZ1.2 (-), D7.2 (A), Q1.3 (D)
/EN: C14.1, J3.3, R8.2, SW1.1, U1.45 (EN)
/I2C1_SCL: J8.1, R23.2, U1.19 (IO15)
/I2C1_SDA: J8.2, R22.2, U1.18 (IO14)
/I2C_INT_SCL: R16.2, U1.17 (IO13), U5.8 (SCL)
/I2C_INT_SDA: R15.2, U1.16 (IO12), U5.7 (SDA)
/LED: R12.1, U1.30 (IO48)
/LED_PWR_A: D5.2 (A), R7.2
/LED_STATUS_A: D6.2 (A), R12.2
/OUT1: R24.1, R25.1, U1.31 (IO35)
/OUT1_COIL: D12.2 (A), D14.1 (K), K1.2, Q2.3 (D)
/OUT1_COM: J9.1, K1.4
/OUT1_G: Q2.1 (G), R24.2
/OUT1_LED_A: D14.2 (A), R26.2
/OUT1_NO: J9.2, K1.3
/OUT2: R27.1, R28.1, U1.32 (IO36)
/OUT2_COIL: D13.2 (A), D15.1 (K), K2.2, Q3.3 (D)
/OUT2_COM: J10.1, K2.4
/OUT2_G: Q3.1 (G), R27.2
/OUT2_LED_A: D15.2 (A), R29.2
/OUT2_NO: J10.2, K2.3
/PAIR: J3.4, R9.2, SW2.1, U1.4 (IO0)
/RTC_INT: R17.2, U1.20 (IO16), U5.3 (~INT/SQW)
/RXD0: J3.8, U1.40 (RXD0)
/S1: D8.3 (COM), R18.2, U1.5 (IO1)
/S1_EXT: J4.4, R18.1
/S2: D9.3 (COM), R19.2, U1.6 (IO2)
/S2_EXT: J5.4, R19.1
/S3: D10.3 (COM), R20.2, U1.7 (IO3)
/S3_EXT: J6.4, R20.1
/S4: D11.3 (COM), R21.2, U1.8 (IO4)
/S4_EXT: J7.4, R21.1
/TXD0: J3.7, U1.39 (TXD0)
/USB_CC1: J2.A5 (CC1), R3.1
/USB_CC2: J2.B5 (CC2), R4.1
/USB_DN: J2.A7 (D-), J2.B7 (D-), J3.5, U1.23 (USB_D-), U3.1 (I/O1), U3.6 (I/O1)
/USB_DP: J2.A6 (D+), J2.B6 (D+), J3.6, U1.24 (USB_D+), U3.3 (I/O2), U3.4 (I/O2)
/VBAT_RTC: BT1.1 (+), U5.6 (VBAT)
/VBUS: F1.1, J2.A4 (VBUS), J2.A9 (VBUS), J2.B4 (VBUS), J2.B9 (VBUS), U3.5 (VBUS)
/VBUS_F: D4.2 (A), F1.2
/VIN: C1.1, C2.1, C3.1, D1.1 (K), D2.1 (A1), R5.1, U2.3 (VIN)
/VIN_RAW: D1.2 (A), J1.1
/VIN_SENSE: C7.1, R5.2, R6.1, U1.14 (IO10)
GND: BT1.2 (-), C1.2, C2.2, C3.2, C5.2, C6.2, C7.2, C8.2, C9.2, C10.2, C11.2, C12.2, C13.2, C14.2, C15.2, C16.2, C17.2, D2.2 (A2), D5.1 (K), D6.1 (K), D8.1 (A), D9.1 (A), D10.1 (A), D11.1 (A), J1.2, J2.A1 (GND), J2.A12 (GND), J2.B1 (GND), J2.B12 (GND), J2.S1 (SHIELD), J3.2, J4.1, J5.1, J6.1, J7.1, J8.4, Q1.2 (S), Q2.2 (S), Q3.2 (S), R2.2, R3.2, R4.2, R6.2, R11.2, R14.2, R25.2, R28.2, SW1.2, SW2.2, U1.1 (GND), U1.2 (GND), U1.42 (GND), U1.43 (GND), U1.46 (GND), U1.47 (GND), U1.48 (GND), U1.49 (GND), U1.50 (GND), U1.51 (GND), U1.52 (GND), U1.53 (GND), U1.54 (GND), U1.55 (GND), U1.56 (GND), U1.57 (GND), U1.58 (GND), U1.59 (GND), U1.60 (GND), U1.61 (GND), U1.62 (GND), U1.63 (GND), U1.64 (GND), U1.65 (GND), U2.1 (GND), U3.2 (GND), U4.2 (GND), U5.5 (GND)

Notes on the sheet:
12 V IN (9-24 V): reverse-polarity diode D1, TVS D2, then the TPS54202 buck set to 5.3 V; D3 drops it to ~5.0 V on the +5V rail.
USB-C: flashing and the serial console (native USB on GPIO19/20), and 5 V for desk use. F1 + D4 feed the +5V rail; CC pull-downs ask for 5 V.
+5V -> 3.3 V: AP7361C (1 A LDO) for the ESP32-S3 (WiFi peaks ~350 mA), the RTC and the 3.3 V sensor supply.
MCU: ESP32-S3-MINI-1-N8 (no PSRAM, so GPIO35-37 stay free). Pins per hardware/pinmap.json, board 'mini'.
Internal I2C (GPIO12/13): DS3231MZ RTC at 0x68 + CR2032 (back side). INT/SQW on GPIO16 can wake the board.
Sensor ports S1-S4 (JST-XH 4-pin: 1 GND, 2 3V3, 3 5V, 4 SIG). SIG: 470R series + BAT54S clamps, so a 5 V digital signal is safe.
Both port supplies are fused (F2, F3). Pull-ups a block needs (DS18B20 4.7k, DHT22 10k) live on the block or its adapter.
I2C-1 student port, Grove pinout (1 SCL, 2 SDA, 3 3V3, 4 GND), on its own bus (GPIO14/15).
Relays OUT1/OUT2 (GPIO35/36): Hongfa HF46F-005 (1 Form A, 5 A, 40 mA coil), low-side AO3400A, flyback diode, coil LED (shows through the lid).
Terminals: 1 COM, 2 NO. Silkscreen: LOW VOLTAGE ONLY (switch a contactor coil, not a pump).

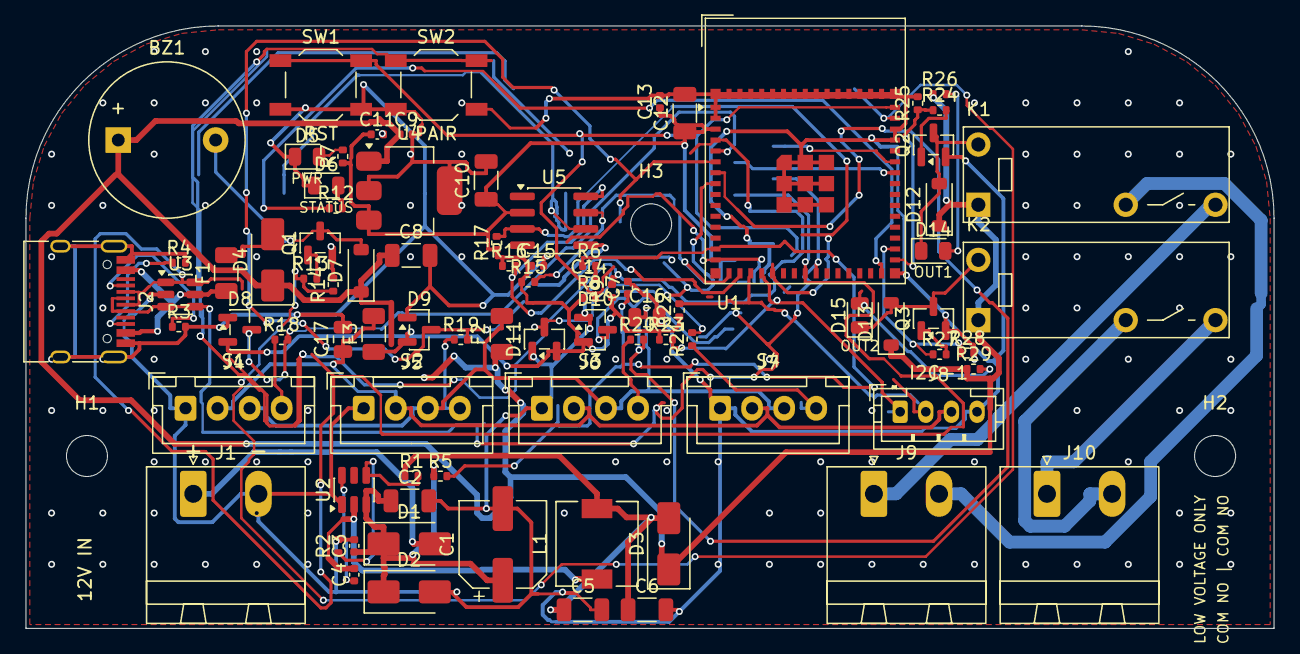
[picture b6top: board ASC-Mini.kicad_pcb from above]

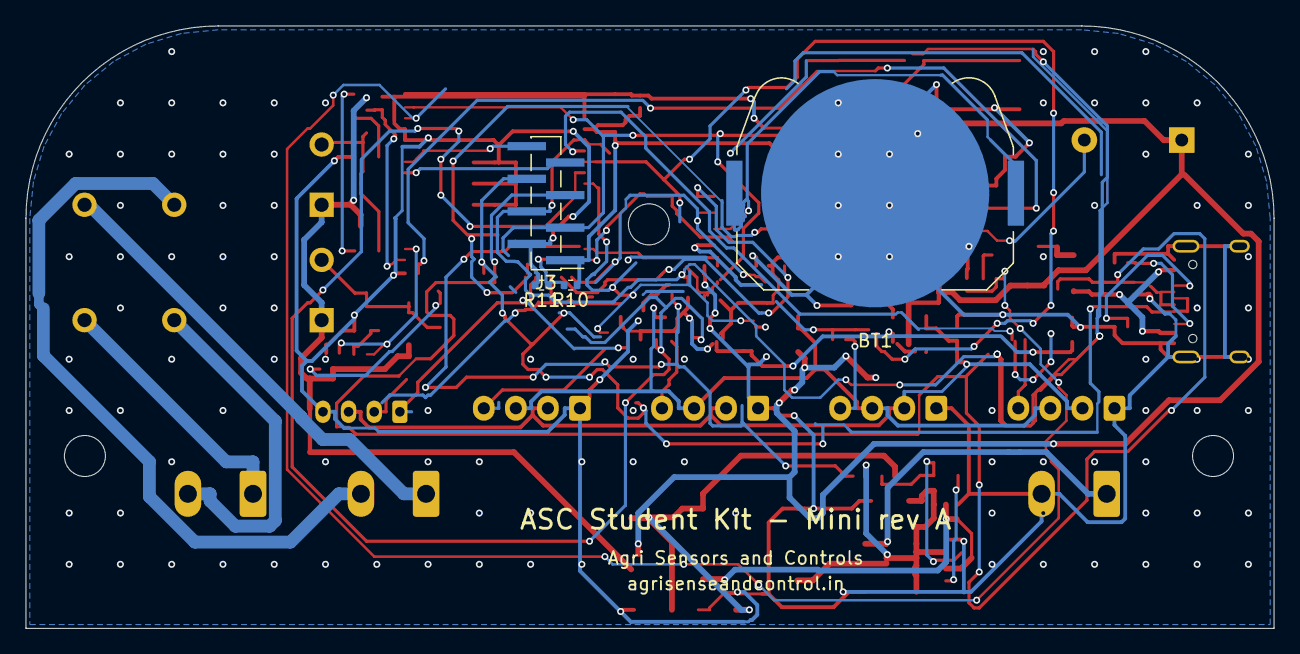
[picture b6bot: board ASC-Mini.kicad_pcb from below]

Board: 2 copper layers, 97.4 x 47.0 mm, 92 parts (4 on the bottom side), 55 nets.
